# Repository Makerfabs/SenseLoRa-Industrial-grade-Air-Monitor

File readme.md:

# SenseLoRa Industrial grade Air Monitor

```c++
/*
Version:		V1.0
Author:			Vincent
Create Date:	2023/9/16
Note:

*/
```
# Makerfabs

[Makerfabs home page](https://www.makerfabs.com/)

[Makerfabs Wiki](https://wiki.makerfabs.com/)

# How To Use

## Arduino Complier Option

**If you have any questions，such as how to install the development board, how to download the code, how to install the library. Please refer to :[Makerfabs_FAQ](https://github.com/Makerfabs/Makerfabs_FAQ)**

- Install board : ESP32 Version 2.0.11
- Select "ESP32-S3"
- Select Erase All Flash
- Upload codes

Arduino libraries:

- RadioLib 4.6.0
- Adafruit_Unified_Sensor 1.1.9
- Adafruit_AHT10 0.1.0
- Adafruit_BusIO 1.14.1
- Adafruit_SGP30_Sensor 2.0.0
- BH1750 1.3.0

## Lora Data Format

```json

{
	"ID": "AirM01",
	"COUNT": 22,
	"SLEEP": 3600,
	"bat": 3.48,
	"temp": 0.00,
	"humi": 0.00,
	"eco2": 0.00,
	"lux": 0.00
}

 ```

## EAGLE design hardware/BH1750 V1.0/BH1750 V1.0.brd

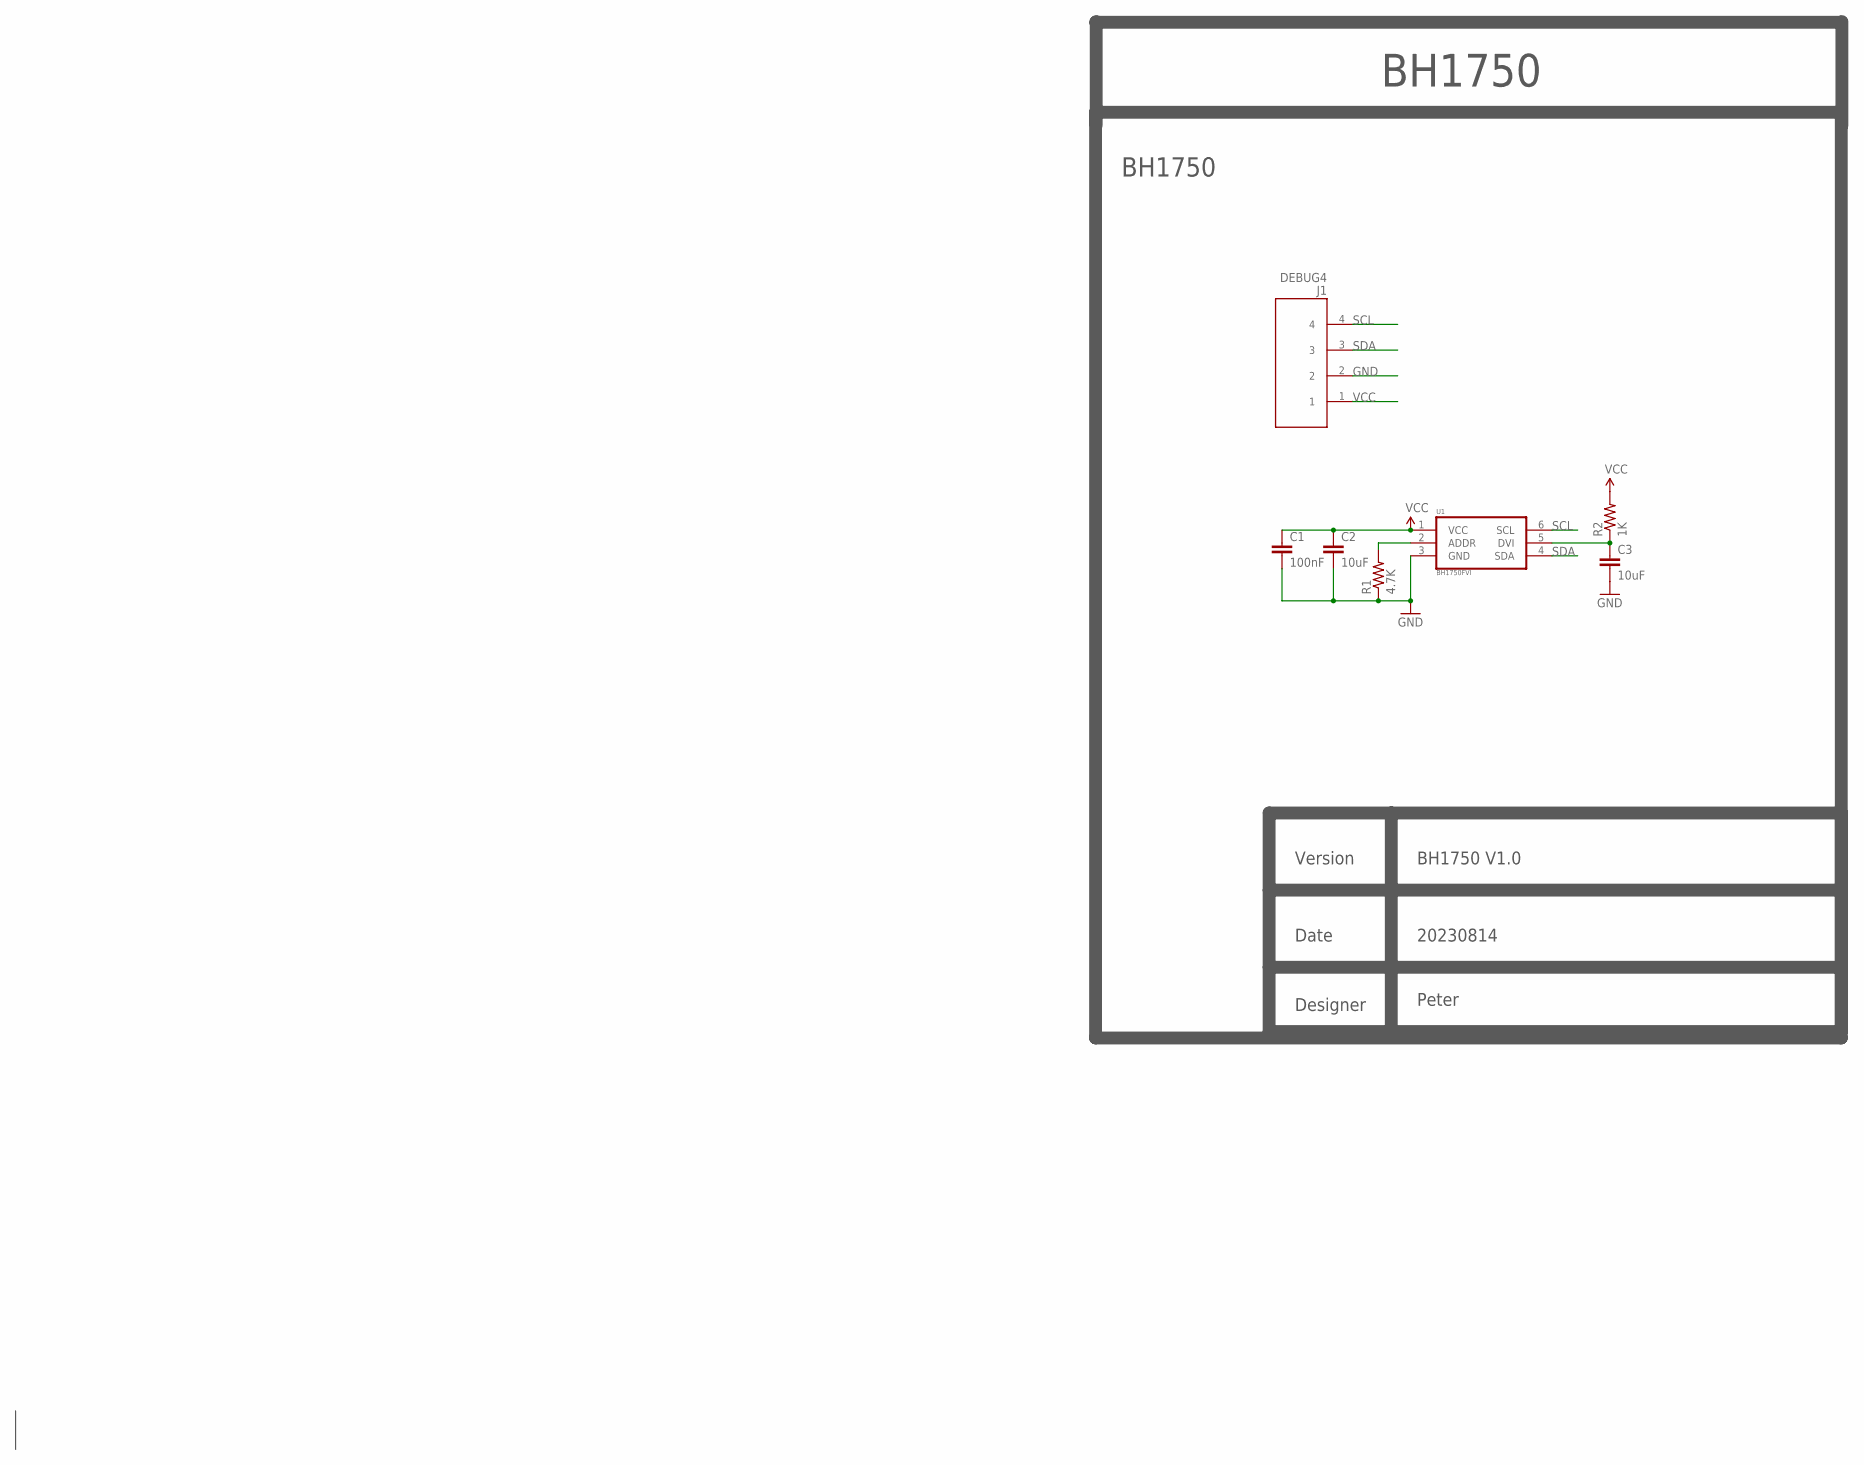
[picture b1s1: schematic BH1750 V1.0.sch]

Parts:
C1: 100nF; C0603
C2, C3: 10uF; C0603
J1: DEBUG4; DEBUG*4
R1: 4.7K; R0603
R2: 1K; R0603
U1: BH1750FVI; WSOF6I

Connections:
GND: C1.2, C2.2, C3.2, J1.2, R1.1, U1.3 (GND)
unnamed: C3.1, R2.1, U1.5 (DVI)
unnamed: R1.2, U1.2 (ADDR)
SCL: J1.4, U1.6 (SCL)
SDA: J1.3, U1.4 (SDA)
VCC: C1.1, C2.1, J1.1, R2.2, U1.1 (VCC)

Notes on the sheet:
BH1750
Version
Date
Designer
BH1750 V1.0
20230814
Peter

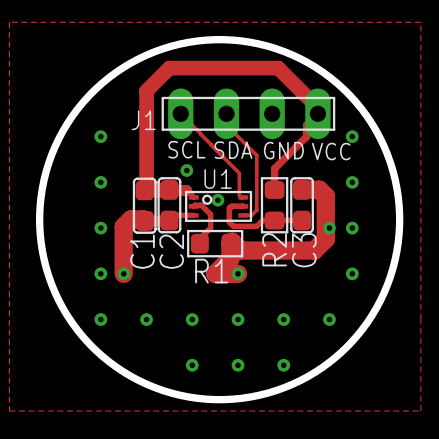
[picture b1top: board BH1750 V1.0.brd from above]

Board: 2 copper layers, 20.0 x 20.0 mm, 7 parts (0 on the bottom side), 6 nets.

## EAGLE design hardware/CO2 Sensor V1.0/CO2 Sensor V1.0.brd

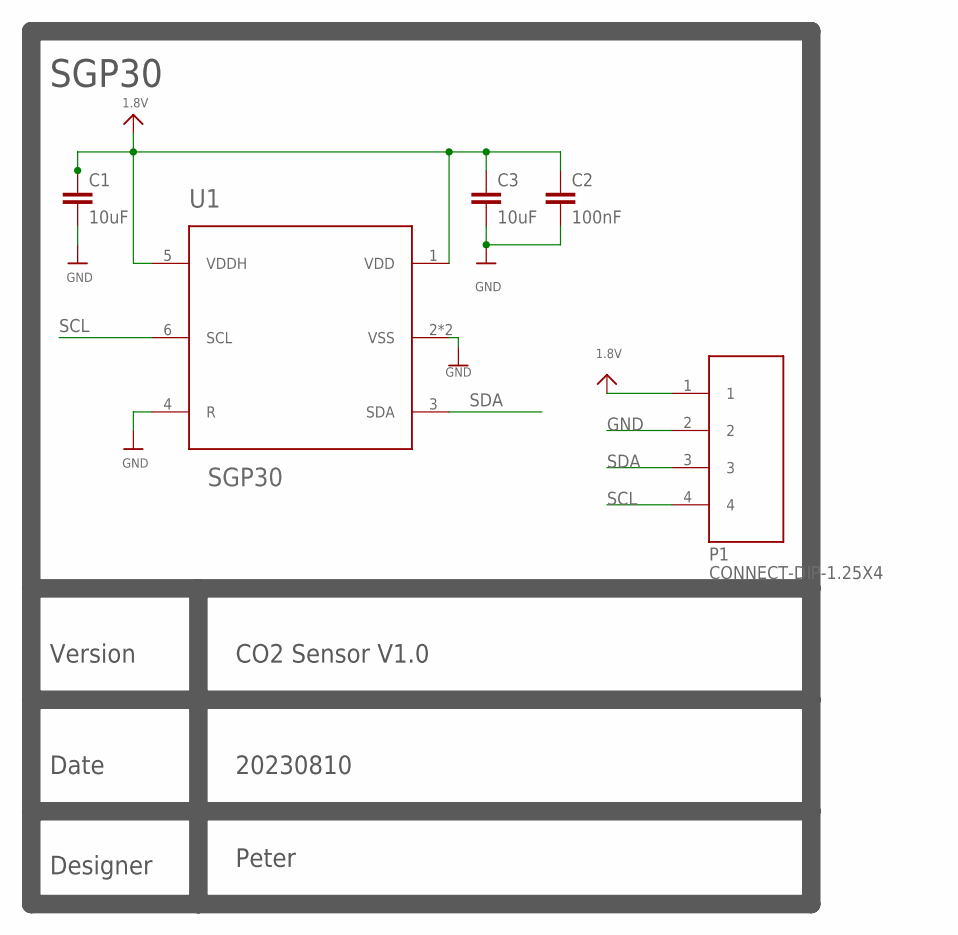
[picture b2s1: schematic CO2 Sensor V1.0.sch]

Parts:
C1, C3: 10uF; C0603
C2: 100nF; C0603
P1: CONNECT-DIP-1.25X4
U1: SGP30

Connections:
1.8V: C1.1, C2.1, C3.1, P1.1, U1.1 (VDD), U1.5 (VDDH)
GND: C1.2, C2.2, C3.2, P1.2, U1.2 (VSS), U1.4 (R), U1.P$7 (VSS)
SCL: P1.4, U1.6 (SCL)
SDA: P1.3, U1.3 (SDA)

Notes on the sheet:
Version
Date
Designer
CO2 Sensor V1.0
20230810
Peter
SGP30

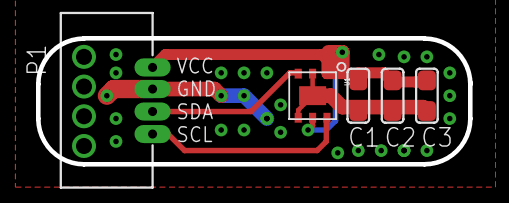
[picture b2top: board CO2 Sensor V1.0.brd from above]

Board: 2 copper layers, 24.0 x 7.0 mm, 5 parts (0 on the bottom side), 4 nets.

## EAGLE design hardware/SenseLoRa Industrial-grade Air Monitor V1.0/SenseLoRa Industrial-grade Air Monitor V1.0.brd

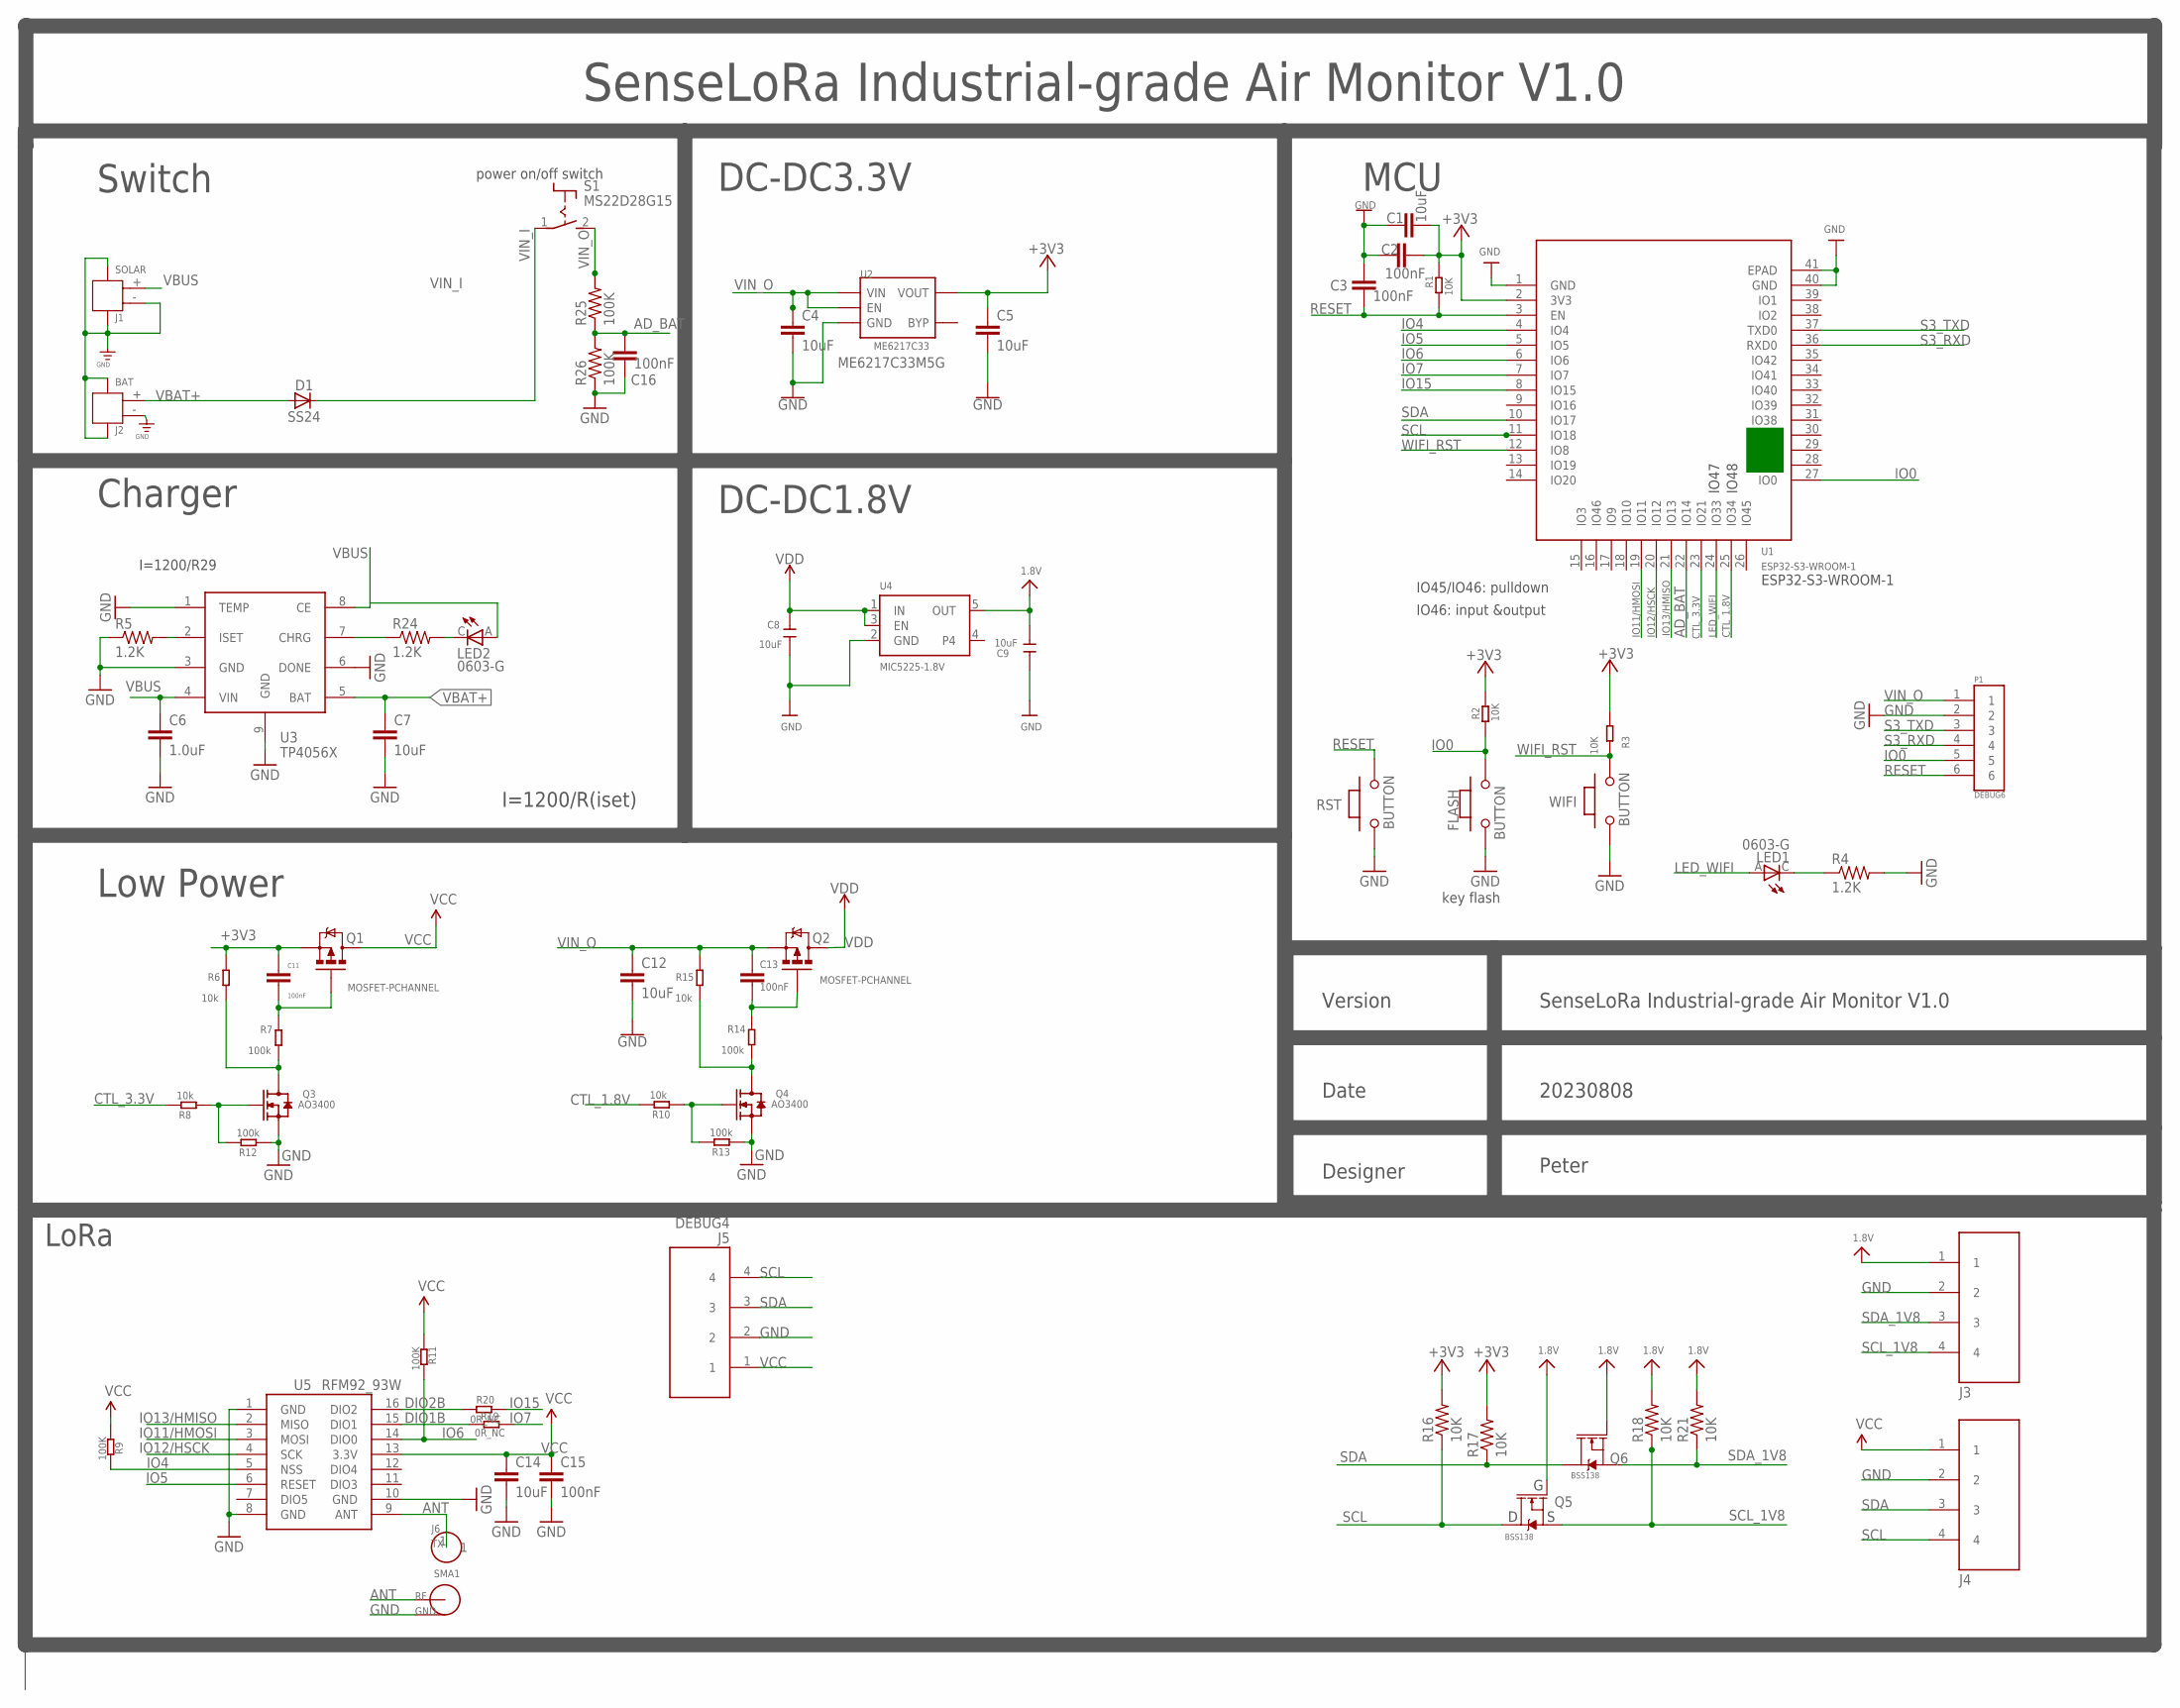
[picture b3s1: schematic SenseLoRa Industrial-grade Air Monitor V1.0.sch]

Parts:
C1, C4, C5, C7, C12, C14: 10uF; C0603
C2, C3, C11, C13, C15, C16: 100nF; C0603
C6: 1.0uF; C0603
C8, C9: 10uF; 0603
D1: SS24; DO-214AC
FLASH: BUTTON; 157SW
J1: SOLAR; HW2-SMD-2.0-90D
J2: BAT; HW2-SMD-2.0-90D
J3, J4: CONNNECT-SMD-1.25X4P
J5: DEBUG4; DEBUG*4
J6: TX; 1P-100/50MIL
LED1, LED2: 0603-G; LED0603
P1: DEBUG6; DEBUG*6
Q1, Q2: MOSFET-PCHANNEL; SOT23-3
Q3, Q4: AO3400; SOT23@1
Q5, Q6: BSS138; SOT23-3
R1, R2, R3, R16, R17, R18, R21: 10K; R0603
R4, R5, R24: 1.2K; R0603
R6, R8, R10, R15: 10k; R0603
R7, R12, R13, R14: 100k; R0603
R9, R11, R25, R26: 100K; R0603
R19, R20: 0R_NC; R0603
RST: BUTTON; 157SW
S1: MS22D28G15; S-MS22D28G15
SMA1: SMA-KWE
U1: ESP32-S3-WROOM-1; ESP32-­S2-­SOLO
U2: ME6217C33; SOT23-5
U3: TP4056X; SOP8-1.27P
U4: MIC5225-1.8V; SOT23-5
U5: RFM92_93W
WIFI: BUTTON; 157SW

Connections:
1.8V: C9.1, J3.1, Q5.1 (G), Q6.1 (G), R18.2, R21.2, U4.5 (OUT)
+3V3: C1.2, C2.2, C5.1, C11.1, Q1.2 (S), R1.2, R2.2, R3.2, R6.2, R16.2, R17.2, U1.2 (3V3), U2.5 (VOUT)
AD_BAT: C16.2, R25.1, R26.2, U1.22 (IO14)
ANT: J6.1, SMA1.1 (SIG), U5.9 (ANT)
CTL_1.8V: R10.2, U1.25 (IO34)
CTL_3.3V: R8.2, U1.23 (IO21)
DIO1B: R19.2, U5.15 (DIO1)
DIO2B: R20.2, U5.16 (DIO2)
GND: C1.1, C2.1, C3.2, C4.2, C5.2, C6.2, C7.2, C8.2, C9.2, C12.2, C14.2, C15.2, C16.1, FLASH.1, J1.3, J1.4, J1.- (2), J2.3, J2.4, J2.- (2), J3.2, J4.2, J5.2, P1.2, Q3.2 (S), Q4.2 (S), R4.2, R5.1, R12.1, R13.1, R26.1, RST.1, SMA1.2 (GND), SMA1.3 (GND), SMA1.4 (GND), SMA1.5 (GND), U1.1 (GND), U1.40 (GND), U1.41 (EPAD), U2.2 (GND), U3.1 (TEMP), U3.3 (GND), U3.6 (DONE), U3.9 (GND), U4.2 (GND), U5.1 (GND), U5.8 (GND), U5.10 (GND), WIFI.1
IO0: FLASH.2, P1.5, R2.1, U1.27 (IO0)
IO4: R9.1, U1.4 (IO4), U5.5 (NSS)
IO5: U1.5 (IO5), U5.6 (RESET)
IO6: R11.1, U1.6 (IO6), U5.14 (DIO0)
IO7: R19.1, U1.7 (IO7)
IO11/HMOSI: U1.19 (IO11), U5.3 (MOSI)
IO12/HSCK: U1.20 (IO12), U5.4 (SCK)
IO13/HMISO: U1.21 (IO13), U5.2 (MISO)
IO15: R20.1, U1.8 (IO15)
ISET: R5.2, U3.2 (ISET)
LED_WIFI: LED1.A, U1.24 (IO33)
unnamed: LED1.C, R4.1
unnamed: R24.1, U3.7 (CHRG)
unnamed: LED2.C, R24.2
unnamed: C13.2, Q2.1 (G), R14.2
unnamed: Q4.1 (G), R10.1, R13.2
unnamed: C11.2, Q1.1 (G), R7.2
unnamed: Q3.1 (G), R8.1, R12.2
unnamed: Q3.3 (D), R6.1, R7.1
unnamed: Q4.3 (D), R14.1, R15.1
RESET: C3.1, P1.6, R1.1, RST.2, U1.3 (EN)
S3_RXD: P1.4, U1.36 (RXD0)
S3_TXD: P1.3, U1.37 (TXD0)
SCL: J4.4, J5.4, Q5.3 (D), R16.1, U1.11 (IO18)
SCL_1V8: J3.4, Q5.2 (S), R18.1
SDA: J4.3, J5.3, Q6.3 (D), R17.1, U1.10 (IO17)
SDA_1V8: J3.3, Q6.2 (S), R21.1
VBAT+: C7.1, D1.A, J2.+ (1), U3.5 (BAT)
VBUS: C6.1, J1.+ (1), LED2.A, U3.4 (VIN), U3.8 (CE)
VCC: C14.1, C15.1, J4.1, J5.1, Q1.3 (D), R9.2, R11.2, U5.13 (3.3V)
VDD: C8.1, Q2.3 (D), U4.1 (IN), U4.3 (EN)
VIN_I: D1.C, S1.1
VIN_O: C4.1, C12.1, C13.1, P1.1, Q2.2 (S), R15.2, R25.2, S1.2 (S), U2.1 (VIN), U2.3 (EN)
WIFI_RST: R3.1, U1.12 (IO8), WIFI.2

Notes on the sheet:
DC-DC3.3V
I=1200/R29
ME6217C33M5G
Charger
LoRa
power on/off switch
key flash
Switch
MCU
Low Power
IO45/IO46: pulldown
IO46: input &output
ESP32-S3-WROOM-1
IO47
IO48
I=1200/R(iset)
SenseLoRa Industrial-grade Air Monitor V1.0
Version
Date
Designer
20230808
Peter
DC-DC1.8V

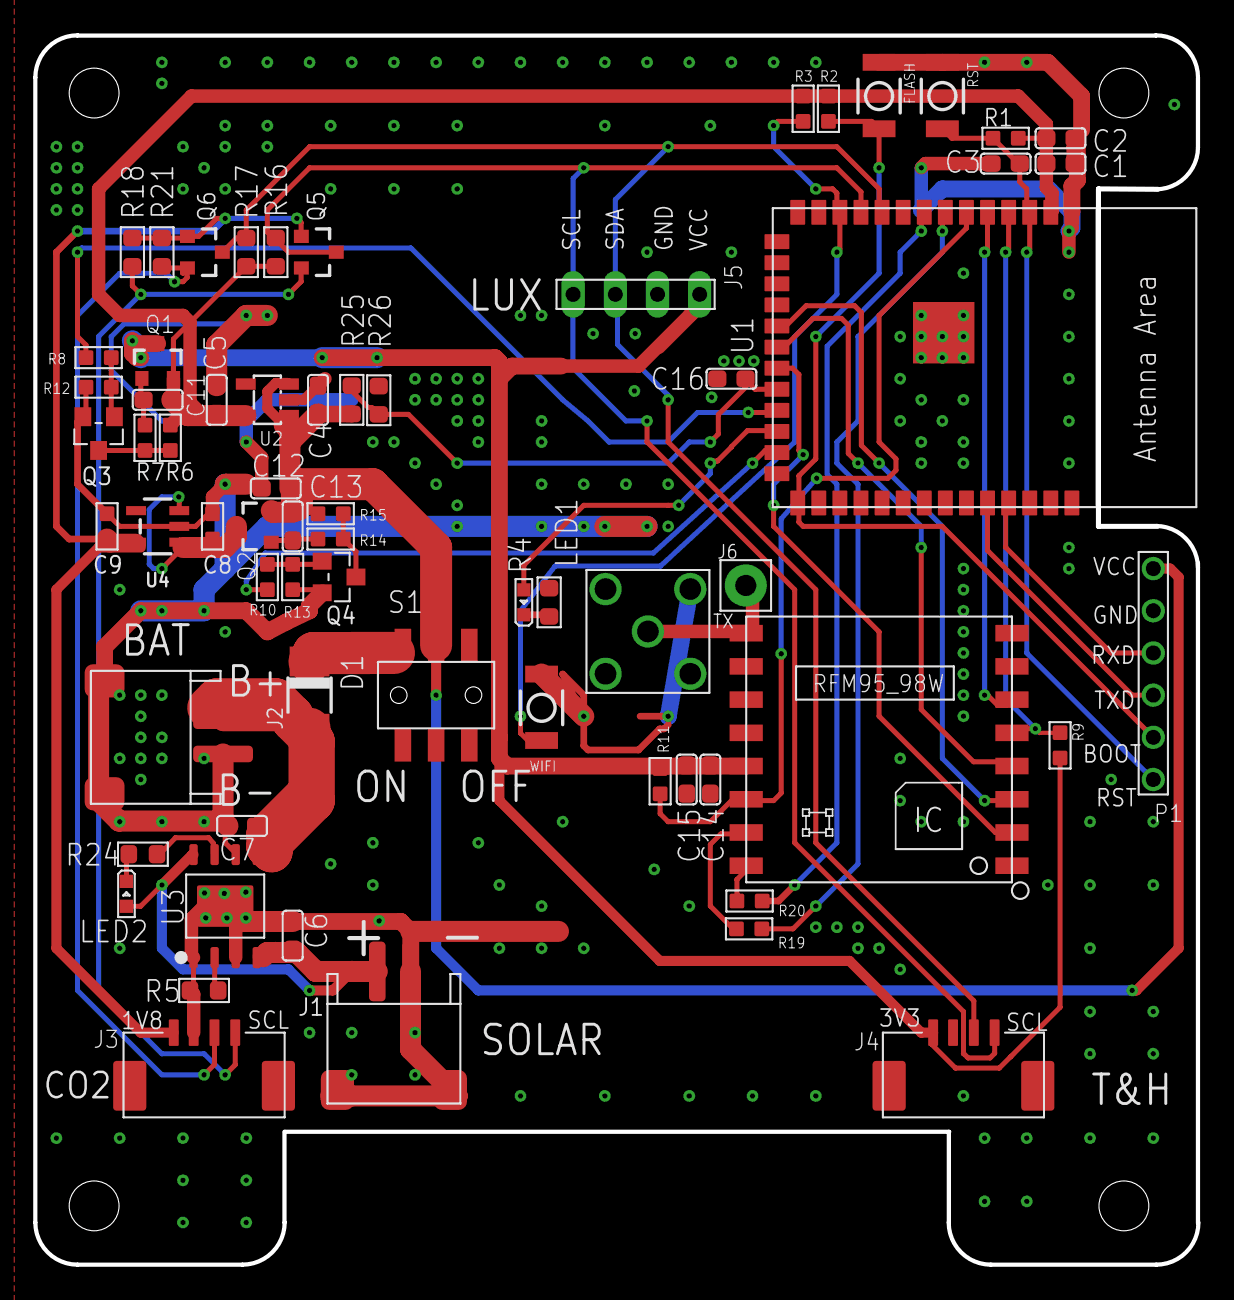
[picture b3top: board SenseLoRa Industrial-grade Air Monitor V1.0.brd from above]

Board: 2 copper layers, 70.0 x 74.0 mm, 66 parts (1 on the bottom side), 43 nets.

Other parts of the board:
U$2: MAKERFABS_0.3

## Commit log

2023-09-16 Create
2023-09-18 Add hardware

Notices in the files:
parts and their libraries:
SparkFun-Aesthetics: Licensing: Creative Commons ShareAlike 4.0 International - https://creativecommons.org/licenses/by-sa/4.0
microbuilder: This work is placed in the public domain, and may be freely used for commercial and non-commercial work with the following conditions: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
